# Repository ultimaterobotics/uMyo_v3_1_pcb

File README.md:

# uMyo_v3_1_pcb
PCB files for uMyo v3.1

This is a KiCAD 6 project for the latest (as of upload date) version of uMyo boards.

PCB is licensed under CERN-OHL-P-2.0 - we use MIT license for our software/firmware projects, but it seems that for hardware it doesn't work well, so we applied this option. In our understanding, it should permit anyone to use this design as a whole or incorporate its parts into other projects with no restrictions (including commercial use), except for claiming that it was not derived from our project. If you want to use it but something in this license prevents you from doing that - please contact us, we'll see what can be done about it.

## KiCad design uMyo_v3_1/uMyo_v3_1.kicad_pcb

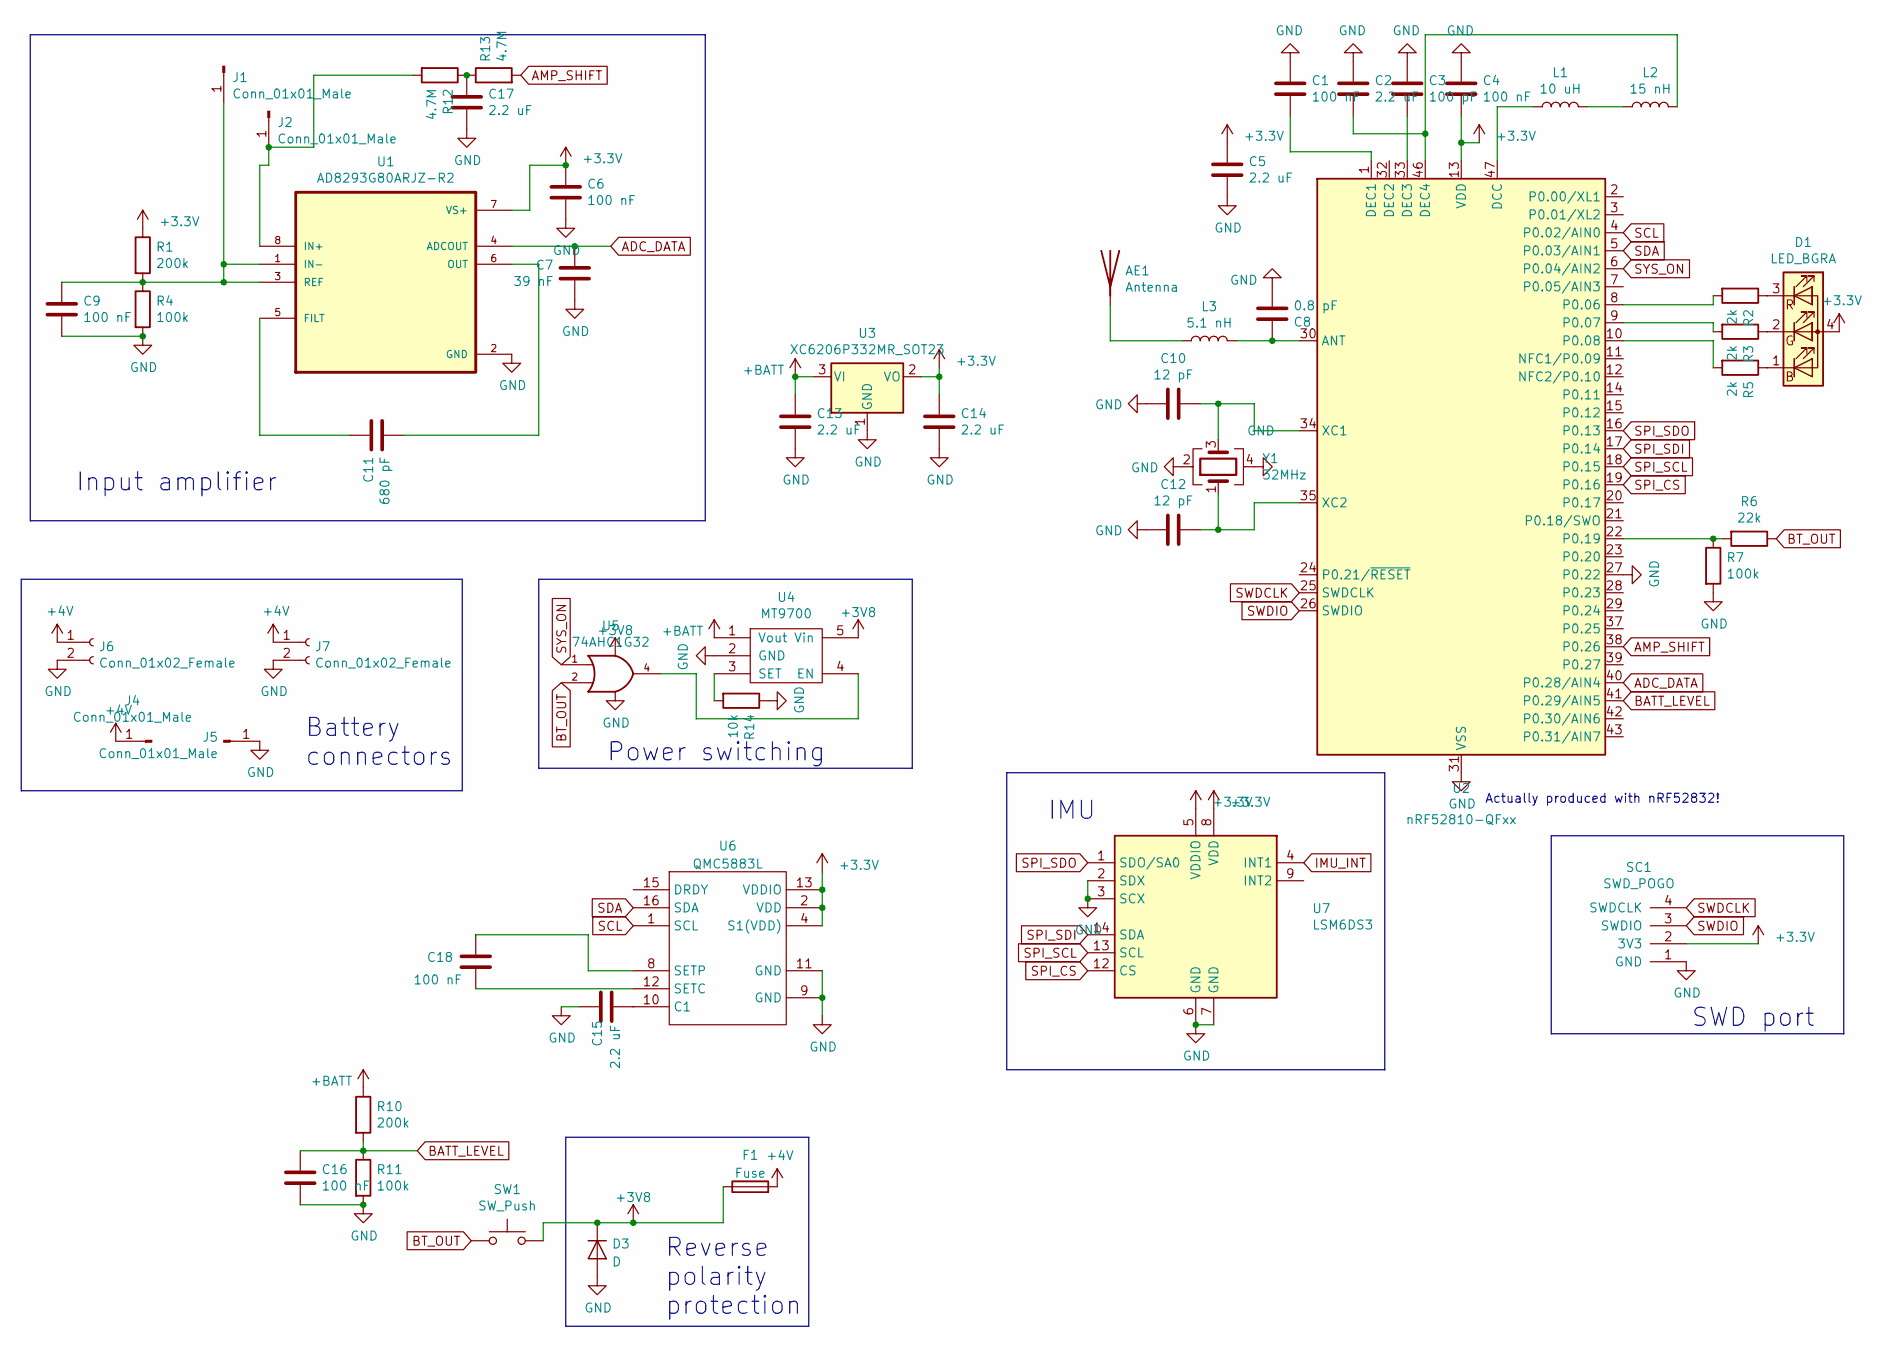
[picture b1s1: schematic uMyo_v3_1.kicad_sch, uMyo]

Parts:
AE1: Antenna; KH3216-A55; JLCPN C484541
C1, C4, C6, C9, C16, C18: 100 nF; C_0402_1005Metric; JLCPN C1525
C2, C5, C13, C14, C15, C17: 2.2 uF; C_0402_1005Metric; JLCPN C12530
C3: 100 pF; C_0402_1005Metric; JLCPN C1546
C7: 39 nF; C_0402_1005Metric; JLCPN C117753
C8: 0.8 pF; C_0402_1005Metric; JLCPN C88902
C10, C12: 12 pF; C_0402_1005Metric; JLCPN C1547
C11: 680 pF; C_0402_1005Metric; JLCPN C113781
D1: LED_BGRA; LED_RGB_0603_a4; JLCPN C282128
D3: D; D_SOD-323; JLCPN C191023
F1: Fuse; Fuse_0603_1608Metric; JLCPN C207011
J1, J2: Conn_01x01_Male; uMyo_dry_connector
J4, J5: Conn_01x01_Male; conn_16_20
J6, J7: Conn_01x02_Female; JST_PH_S2B-PH-SM4-TB_1x02-1MP_P2.00mm_Horizontal; JLCPN C520130
L1: 10 uH; L_0603_1608Metric; JLCPN C1035
L2: 15 nH; L_0402_1005Metric; JLCPN C27143
L3: 5.1 nH; L_0402_1005Metric; JLCPN C86066
R1, R10: 200k; R_0402_1005Metric; JLCPN C25764
R2, R3, R5: 2k; R_0402_1005Metric; JLCPN C4109
R4, R7, R11: 100k; R_0402_1005Metric; JLCPN C25741
R6: 22k; R_0402_1005Metric; JLCPN C25768
R12, R13: 4.7M; R_0402_1005Metric; JLCPN C227116
R14: 10k; R_0402_1005Metric; JLCPN C25744
SC1: SWD_POGO
SW1: SW_Push; SW_SPST_CK_RS282G05A3; JLCPN C2845294
U1: AD8293G80ARJZ-R2; SOT-23-8; JLCPN C141950
U2: nRF52810-QFxx; QFN-48-1EP_6x6mm_Pitch0.4mm; JLCPN C141828
U3: XC6206P332MR_SOT23; SOT-23; JLCPN C5446
U4: MT9700; SOT-23-5; JLCPN C89855
U5: 74AHC1G32; SOT-23-5; JLCPN C507209
U6: QMC5883L; LGA-16_3x3mm_P0.5mm; JLCPN C976032
U7: LSM6DS3; LGA-14_3x2.5mm_P0.5mm_LayoutBorder3x4y; JLCPN C967633
Y1: 32MHz; Crystal_SMD_2016-4Pin_2.0x1.6mm; JLCPN C843260

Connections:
+3V3: C4.1, C5.2, C6.2, C14.2, D1.4 (A), R1.1, SC1.2 (3V3), U1.7 (VS+), U2.13 (VDD), U2.36 (VDD), U2.48 (VDD), U3.2 (VO), U6.2 (VDD), U6.4 (S1(VDD)), U6.13 (VDDIO), U7.5 (VDDIO), U7.8 (VDD)
+3V8: D3.1 (K), F1.1, SW1.2, U4.5 (Vin), U5.5 (VCC)
+4V: F1.2, J4.1, J6.1, J7.1
+BATT: C13.2, R10.1, U3.3 (VI), U4.1 (Vout)
ADC_DATA: C7.1, U1.4 (ADCOUT), U2.40 (P0.28/AIN4)
AMP_SHIFT: R13.2, U2.38 (P0.26)
BATT_LEVEL: C16.2, R10.2, R11.1, U2.41 (P0.29/AIN5)
BT_OUT: R6.1, SW1.1, U5.2
GND: C1.2, C2.2, C3.2, C4.2, C5.1, C6.1, C7.2, C8.2, C9.1, C10.1, C12.1, C13.1, C14.1, C15.2, C16.1, C17.1, D3.2 (A), J5.1, J6.2, J7.2, R4.2, R7.2, R11.2, R14.1, SC1.1 (GND), U1.2 (GND), U2.27 (P0.22), U2.31 (VSS), U2.45 (VSS), U2.49 (VSS), U3.1 (GND), U4.2 (GND), U5.3 (GND), U6.9 (GND), U6.11 (GND), U7.2 (SDX), U7.3 (SCX), U7.6 (GND), U7.7 (GND), Y1.2, Y1.4
IMU_INT: U7.4 (INT1)
unnamed: AE1.1 (A), L3.1
unnamed: C1.1, U2.1 (DEC1)
unnamed: C2.1, L2.2, U2.46 (DEC4)
unnamed: C3.1, U2.33 (DEC3)
unnamed: C8.1, L3.2, U2.30 (ANT)
unnamed: C9.2, J1.1, R1.2, R4.1, U1.1 (IN-), U1.3 (REF)
unnamed: C10.2, U2.34 (XC1), Y1.3
unnamed: C11.1, U1.5 (FILT)
unnamed: C11.2, U1.6 (OUT)
unnamed: C12.2, U2.35 (XC2), Y1.1
unnamed: C15.1, U6.10 (C1)
unnamed: C17.2, R12.1, R13.1
unnamed: C18.1, U6.12 (SETC)
unnamed: C18.2, U6.8 (SETP)
unnamed: D1.1 (BK), R5.1
unnamed: D1.2 (GK), R3.1
unnamed: D1.3 (RK), R2.1
unnamed: J2.1, R12.2, U1.8 (IN+)
unnamed: L1.1, U2.47 (DCC)
unnamed: L1.2, L2.1
unnamed: R2.2, U2.8 (P0.06)
unnamed: R3.2, U2.9 (P0.07)
unnamed: R5.2, U2.10 (P0.08)
unnamed: R6.2, R7.1, U2.22 (P0.19)
unnamed: R14.2, U4.3 (SET)
unnamed: U4.4 (EN), U5.4
SCL: U2.4 (P0.02/AIN0), U6.1 (SCL)
SDA: U2.5 (P0.03/AIN1), U6.16 (SDA)
SPI_CS: U2.19 (P0.16), U7.12 (CS)
SPI_SCL: U2.18 (P0.15), U7.13 (SCL)
SPI_SDI: U2.17 (P0.14), U7.14 (SDA)
SPI_SDO: U2.16 (P0.13), U7.1 (SDO/SA0)
SWDCLK: SC1.4 (SWDCLK), U2.25 (SWDCLK)
SWDIO: SC1.3 (SWDIO), U2.26 (SWDIO)
SYS_ON: U2.6 (P0.04/AIN2), U5.1

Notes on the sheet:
SWD port
Power switching
Battery connectors
IMU
Reverse polarity protection
Actually produced with nRF52832!
Input amplifier

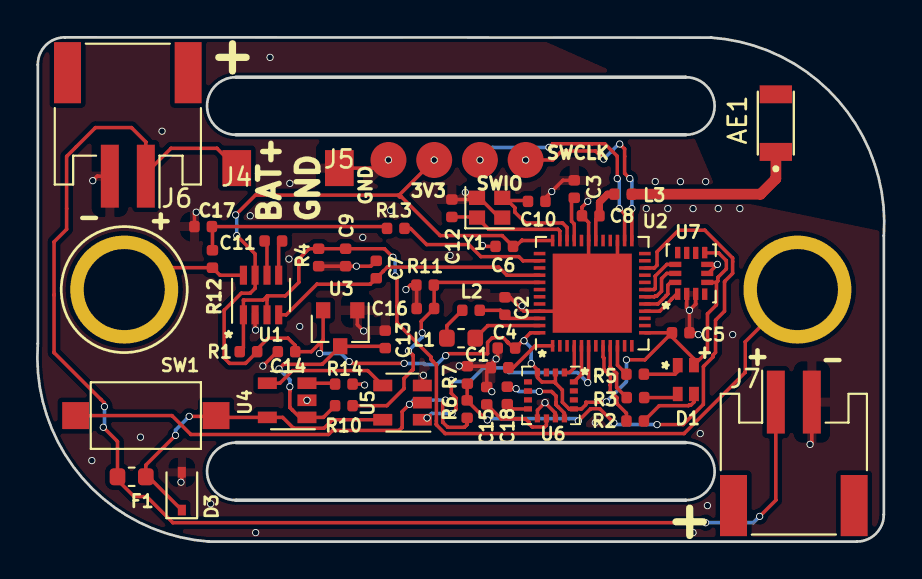
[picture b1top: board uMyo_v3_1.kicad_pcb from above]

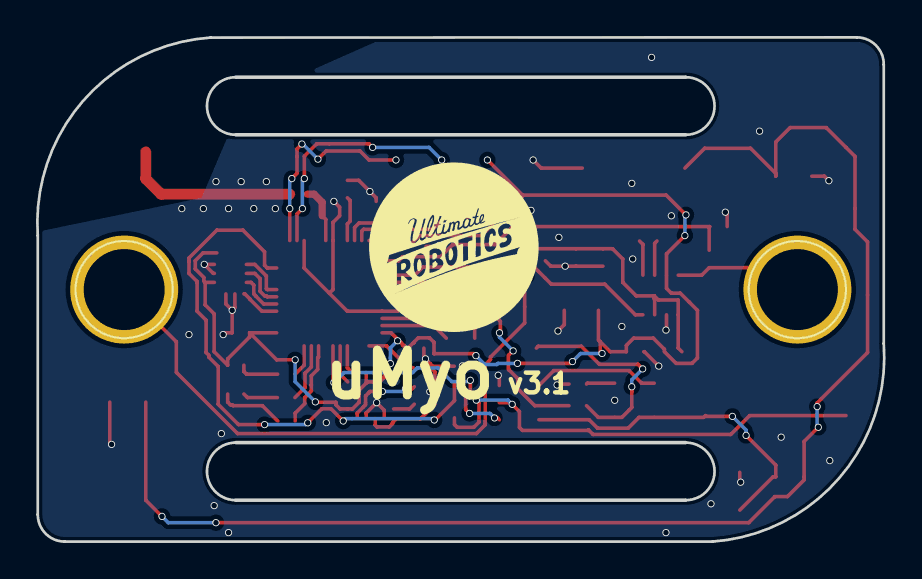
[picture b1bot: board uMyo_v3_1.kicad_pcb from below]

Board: 2 copper layers, 47.0 x 28.0 mm, 53 parts (2 on the bottom side), 44 nets.

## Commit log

2024-05-14 Added KiCAD PCB files
    Initial upload of all KiCAD files for uMyo v3_1
2024-05-14 Created LICENSE
    Added CERN Open Hardware Licence Version 2
2024-05-14 Update README.md
    Added more details about the files and license
2024-05-15 Delete uMyo_v3_1/README.md
    old file from v2 folder
2024-05-15 Delete uMyo_v3_1/uMyo_v3_1.pdf
    old version (for v2), will be replaced by correct one
2024-05-15 Uploaded v3.1 schematics in PDF
    The old file in the folder was from v2, replaced with correct one
